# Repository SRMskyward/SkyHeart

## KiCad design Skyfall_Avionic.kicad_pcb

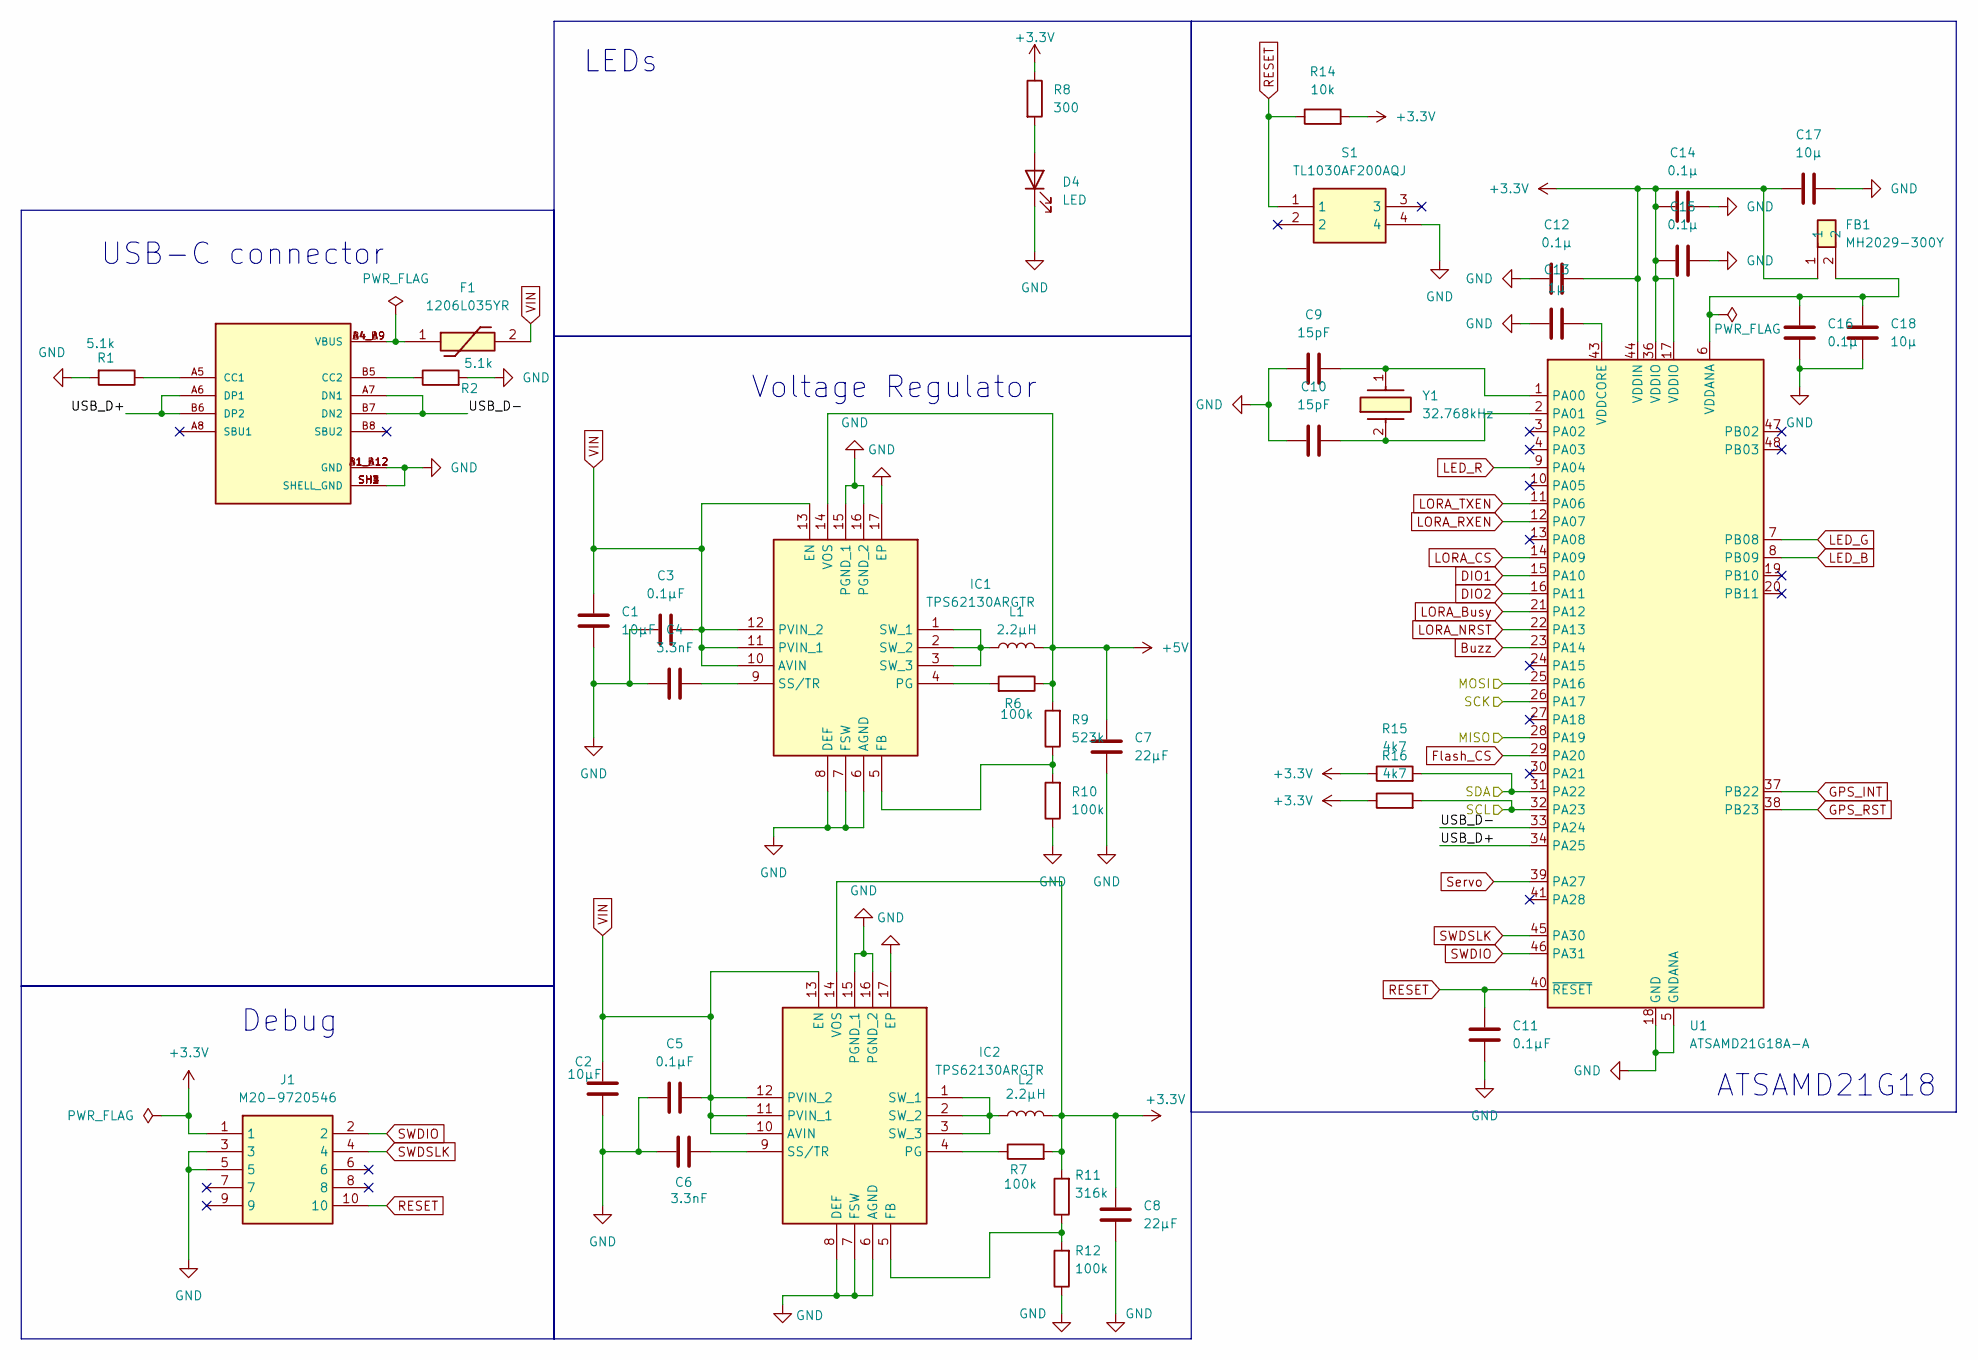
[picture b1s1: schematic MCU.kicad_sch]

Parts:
C1, C2: 10µF; C_0603_1608Metric
C3, C5, C11: 0.1µF; C_0603_1608Metric
C4, C6: 3.3nF; C_0603_1608Metric
C7, C8: 22µF; C_0603_1608Metric
C9, C10: 15pF; C_0603_1608Metric
C12, C14, C15, C16: 0.1µ; C_0603_1608Metric
C13: 1µ; C_0603_1608Metric
C17, C18: 10µ; C_0603_1608Metric
D4: LED; LED_0805_2012Metric
F1: 1206L035YR; 1206L05015YR; Mouser Part Number 576-1206L035YR
FB1: MH2029-300Y; BEADC2016X130N; Mouser Part Number 652-MH2029-300Y
IC1, IC2: TPS62130ARGTR; QFN50P300X300X100-17N-D; Mouser Part Number 595-TPS62130ARGTR
J1: M20-9720546; HDRV10W64P254_2X5_1270X508X954P; Mouser Part Number 855-M20-9720546
J2: USB4105-GF-A-060; GCT_USB4105-GF-A-060; PARTREV B3
L1, L2: 2.2µH; L_TDK_NLV32_3.2x2.5mm
R1, R2: 5.1k; R_0603_1608Metric
R6, R7, R10, R12: 100k; R_0603_1608Metric
R8: 300; R_0603_1608Metric
R9: 523k; R_0603_1608Metric
R11: 316k; R_0603_1608Metric
R14: 10k; R_0603_1608Metric
R15, R16: 4k7; R_0603_1608Metric
S1: TL1030AF200AQJ; Mouser Part Number 612-TL1030AF200AQJ
U1: ATSAMD21G18A-A; TQFP-48_7x7mm_P0.5mm
Y1: 32.768kHz; VMK3900132K7680000; Mouser Part Number 579-K3900132K7680000

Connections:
+3.3V: C8.2, C12.1, C14.2, C15.2, C17.2, FB1.1, IC2.14 (VOS), J1.1, L2.2, R7.2, R8.1, R11.2, R14.2, R15.1, R16.1, U1.17 (VDDIO), U1.36 (VDDIO), U1.44 (VDDIN); also elsewhere on the board
+5V: C7.2, IC1.14 (VOS), L1.2, R6.1, R9.2; also elsewhere on the board
/Actionners_&_connectors/MISO: U1.28 (PA19); also elsewhere on the board
/Actionners_&_connectors/MOSI: U1.25 (PA16); also elsewhere on the board
/Actionners_&_connectors/SCK: U1.26 (PA17); also elsewhere on the board
/Actionners_&_connectors/SCL: R16.2, U1.32 (PA23); also elsewhere on the board
/Actionners_&_connectors/SDA: R15.2, U1.31 (PA22); also elsewhere on the board
/MCU/USB_D+: J2.A6 (DP1), J2.B6 (DP2), U1.34 (PA25)
/MCU/USB_D-: J2.A7 (DN1), J2.B7 (DN2), U1.33 (PA24)
Buzz: U1.23 (PA14); also elsewhere on the board
DIO1: U1.15 (PA10); also elsewhere on the board
DIO2: U1.16 (PA11); also elsewhere on the board
Flash_CS: U1.29 (PA20); also elsewhere on the board
GND: C1.1, C2.1, C3.1, C4.1, C5.1, C6.1, C7.1, C8.1, C9.2, C10.2, C11.2, C12.2, C13.2, C14.1, C15.1, C16.2, C17.1, C18.2, D4.1 (K), IC1.6 (AGND), IC1.7 (FSW), IC1.8 (DEF), IC1.15 (PGND_1), IC1.16 (PGND_2), IC1.17 (EP), IC2.6 (AGND), IC2.7 (FSW), IC2.8 (DEF), IC2.15 (PGND_1), IC2.16 (PGND_2), IC2.17 (EP), J1.3, J1.5, J2.A1_B12 (GND), J2.B1_A12 (GND), J2.SH1 (SHELL_GND), J2.SH2 (SHELL_GND), J2.SH3 (SHELL_GND), J2.SH4 (SHELL_GND), R1.2, R2.2, R10.1, R12.1, S1.4, U1.5 (GNDANA), U1.18 (GND), U1.35 (GND), U1.42 (GND); also elsewhere on the board
GPS_INT: U1.37 (PB22)
GPS_RST: U1.38 (PB23)
LED_B: U1.8 (PB09); also elsewhere on the board
LED_G: U1.7 (PB08); also elsewhere on the board
LED_R: U1.9 (PA04); also elsewhere on the board
LORA_Busy: U1.21 (PA12); also elsewhere on the board
LORA_CS: U1.14 (PA09); also elsewhere on the board
LORA_NRST: U1.22 (PA13); also elsewhere on the board
LORA_RXEN: U1.12 (PA07); also elsewhere on the board
LORA_TXEN: U1.11 (PA06); also elsewhere on the board
unnamed: D4.2 (A), R8.2
unnamed: F1.1, J2.A4_B9 (VBUS), J2.B4_A9 (VBUS)
unnamed: IC1.5 (FB), R9.1, R10.2
unnamed: IC1.4 (PG), R6.2
unnamed: C4.2, IC1.9 (SS/TR)
unnamed: IC1.1 (SW_1), IC1.2 (SW_2), IC1.3 (SW_3), L1.1
unnamed: IC2.5 (FB), R11.1, R12.2
unnamed: IC2.4 (PG), R7.1
unnamed: C6.2, IC2.9 (SS/TR)
unnamed: IC2.1 (SW_1), IC2.2 (SW_2), IC2.3 (SW_3), L2.1
unnamed: J2.A5 (CC1), R1.1
unnamed: J2.B5 (CC2), R2.1
unnamed: C9.1, U1.1 (PA00), Y1.1 (CRYSTAL)
unnamed: C10.1, U1.2 (PA01), Y1.2 (CRYSTAL)
unnamed: C16.1, C18.1, FB1.2, U1.6 (VDDANA)
unnamed: C13.1, U1.43 (VDDCORE)
RESET: C11.1, J1.10, R14.1, S1.1, U1.40 (~RESET)
SWDIO: J1.2, U1.46 (PA31)
SWDSLK: J1.4, U1.45 (PA30)
Servo: U1.39 (PA27); also elsewhere on the board
VIN: C1.2, C2.2, C3.2, C5.2, F1.2, IC1.10 (AVIN), IC1.11 (PVIN_1), IC1.12 (PVIN_2), IC1.13 (EN), IC2.10 (AVIN), IC2.11 (PVIN_1), IC2.12 (PVIN_2), IC2.13 (EN); also elsewhere on the board

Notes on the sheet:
ATSAMD21G18
USB-C connector
LEDs
Voltage Regulator
Debug

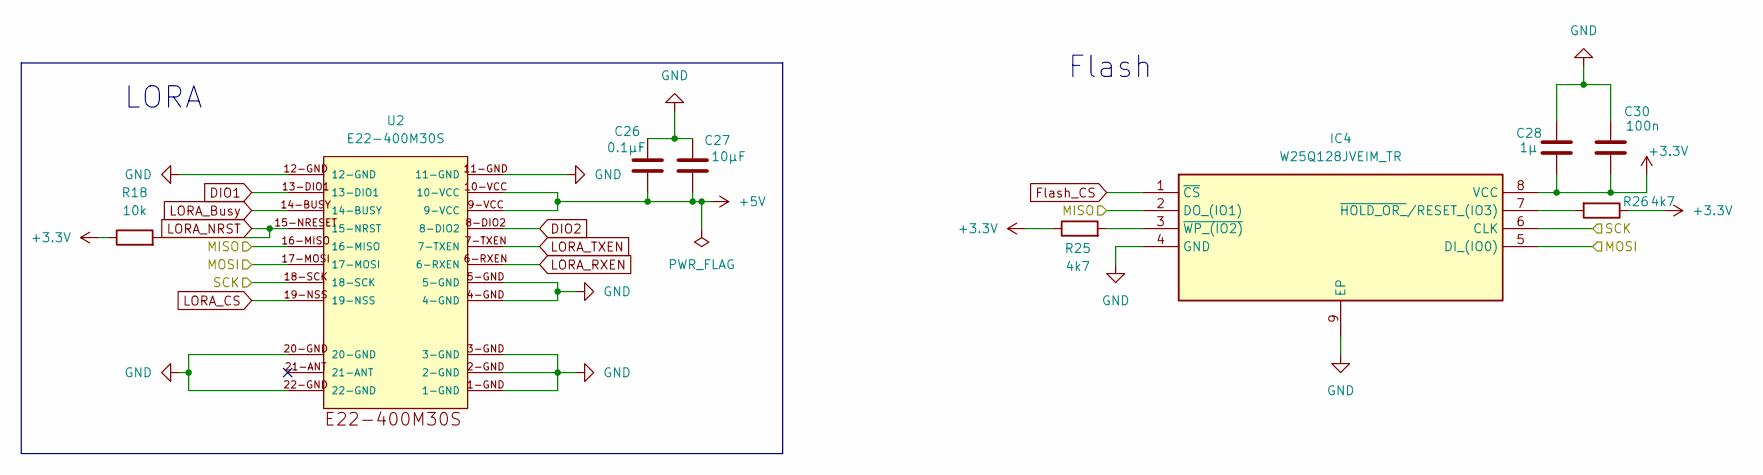
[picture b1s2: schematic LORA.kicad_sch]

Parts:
C26: 0.1µF; C_0603_1608Metric
C27: 10µF; C_0603_1608Metric
C28: 1µ; C_0603_1608Metric
C30: 100n; C_0603_1608Metric
IC4: W25Q128JVEIM_TR; SON127P800X600X80-9N-D; Mouser Part Number 454-W25Q128JVEIMTR
R18: 10k; R_0603_1608Metric
R25, R26: 4k7; R_0603_1608Metric
U2: E22-400M30S

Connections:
+3.3V: C28.1, C30.1, IC4.8 (VCC), R18.1, R25.1, R26.1; also elsewhere on the board
+5V: C26.1, C27.1, U2.9-VCC, U2.10-VCC; also elsewhere on the board
/Actionners_&_connectors/MISO: IC4.2 (DO_(IO1)), U2.16-MISO; also elsewhere on the board
/Actionners_&_connectors/MOSI: IC4.5 (DI_(IO0)), U2.17-MOSI; also elsewhere on the board
/Actionners_&_connectors/SCK: IC4.6 (CLK), U2.18-SCK; also elsewhere on the board
DIO1: U2.13-DIO1; also elsewhere on the board
DIO2: U2.8-DIO2; also elsewhere on the board
Flash_CS: IC4.1 (~CS); also elsewhere on the board
GND: C26.2, C27.2, C28.2, C30.2, IC4.4 (GND), IC4.9 (EP), U2.1-GND, U2.2-GND, U2.3-GND, U2.4-GND, U2.5-GND, U2.11-GND, U2.12-GND, U2.20-GND, U2.22-GND; also elsewhere on the board
LORA_Busy: U2.14-BUSY; also elsewhere on the board
LORA_CS: U2.19-NSS; also elsewhere on the board
LORA_NRST: R18.2, U2.15-NRESET (15-NRST); also elsewhere on the board
LORA_RXEN: U2.6-RXEN; also elsewhere on the board
LORA_TXEN: U2.7-TXEN; also elsewhere on the board
unnamed: IC4.7 (~HOLD_OR_/RESET_(IO3)), R26.2
unnamed: IC4.3 (~WP_(IO2)), R25.2

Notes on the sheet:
LORA
Flash

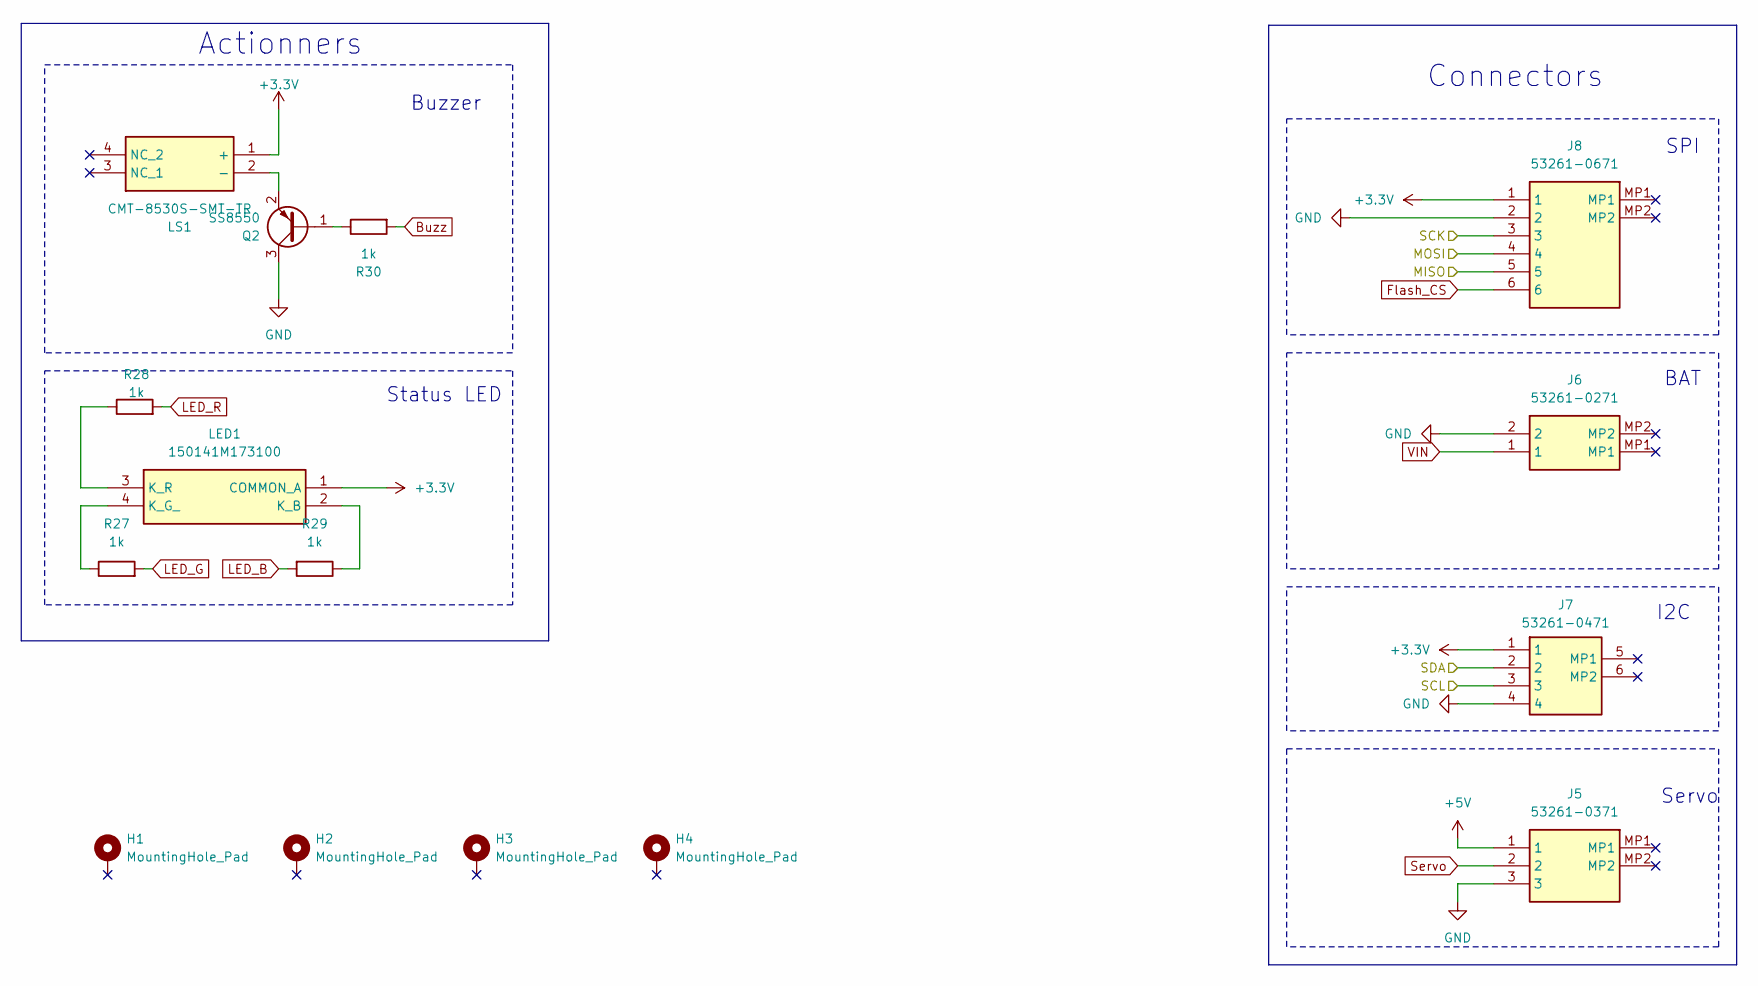
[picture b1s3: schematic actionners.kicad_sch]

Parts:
H1, H2, H3, H4: MountingHole_Pad; MountingHole_2.7mm_M2.5_Pad
J5: 53261-0371; 532610371; Mouser Part Number 538-53261-0371
J6: 53261-0271; 532610271; Mouser Part Number 538-53261-0271
J7: 53261-0471; Mouser Part Number 538-53261-0471
J8: 53261-0671; 532610671; Mouser Part Number 538-53261-0671
LED1: 150141M173100; Mouser Part Number 710-150141M173100
LS1: CMT-8530S-SMT-TR; CMT8530SSMTTR; Mouser Part Number 490-CMT-8530S-SMT-TR
Q2: SS8550; SOT-23
R27, R28, R29, R30: 1k; R_0603_1608Metric

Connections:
+3.3V: J7.1, J8.1, LED1.1 (COMMON_A), LS1.1 (+); also elsewhere on the board
+5V: J5.1; also elsewhere on the board
/Actionners_&_connectors/MISO: J8.5; also elsewhere on the board
/Actionners_&_connectors/MOSI: J8.4; also elsewhere on the board
/Actionners_&_connectors/SCK: J8.3; also elsewhere on the board
/Actionners_&_connectors/SCL: J7.3; also elsewhere on the board
/Actionners_&_connectors/SDA: J7.2; also elsewhere on the board
Buzz: R30.2; also elsewhere on the board
Flash_CS: J8.6; also elsewhere on the board
GND: H1.1, H2.1, H3.1, H4.1, J5.3, J6.2, J7.4, J8.2, Q2.3 (C); also elsewhere on the board
LED_B: R29.2; also elsewhere on the board
LED_G: R27.2; also elsewhere on the board
LED_R: R28.2; also elsewhere on the board
unnamed: LED1.2 (K_B), R29.1
unnamed: LED1.4 (K_G_), R27.1
unnamed: LED1.3 (K_R), R28.1
unnamed: LS1.2 (-), Q2.2 (E)
unnamed: Q2.1 (B), R30.1
Servo: J5.2; also elsewhere on the board
VIN: J6.1; also elsewhere on the board

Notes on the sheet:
Buzzer
Actionners
Status LED
BAT
SPI
Servo
I2C
Connectors

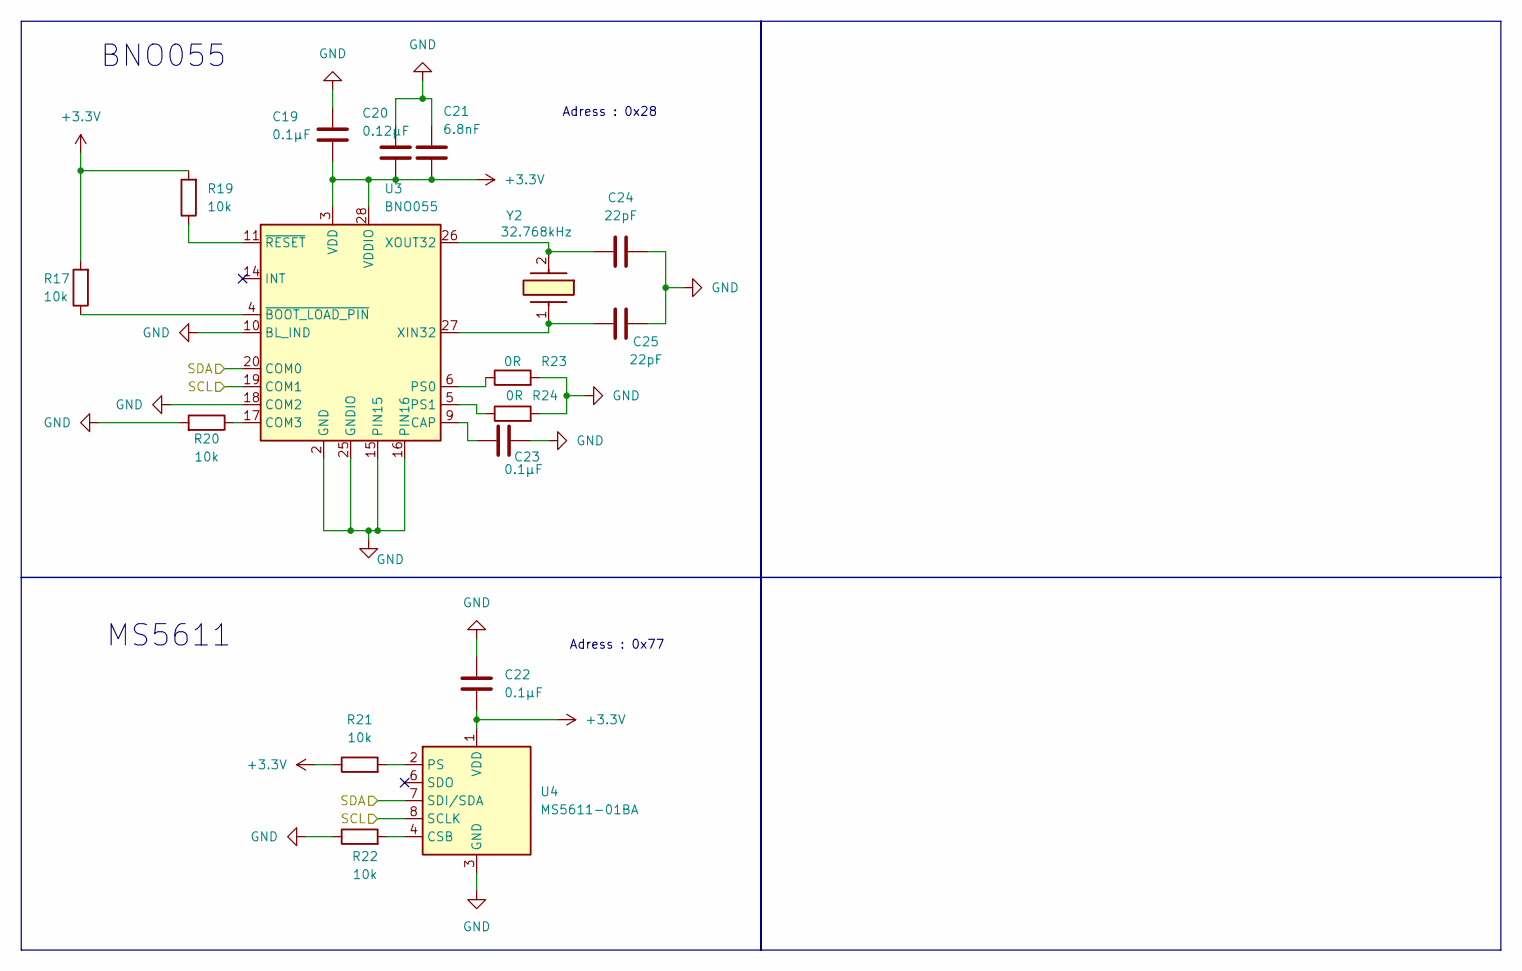
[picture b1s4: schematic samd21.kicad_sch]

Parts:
C19, C22, C23: 0.1µF; C_0603_1608Metric
C20: 0.12µF; C_0603_1608Metric
C21: 6.8nF; C_0603_1608Metric
C24, C25: 22pF; C_0603_1608Metric
R17, R19, R20, R21, R22: 10k; R_0603_1608Metric
R23, R24: 0R; R_0603_1608Metric
U3: BNO055; LGA-28_5.2x3.8mm_P0.5mm
U4: MS5611-01BA; LGA-8_3x5mm_P1.25mm
Y2: 32.768kHz; VMK3900132K7680000; Mouser Part Number 579-K3900132K7680000

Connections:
+3.3V: C19.1, C20.1, C21.1, C22.1, R17.2, R19.2, R21.1, U3.3 (VDD), U3.28 (VDDIO), U4.1 (VDD); also elsewhere on the board
/Actionners_&_connectors/SCL: U3.19 (COM1), U4.8 (SCLK); also elsewhere on the board
/Actionners_&_connectors/SDA: U3.20 (COM0), U4.7 (SDI/SDA); also elsewhere on the board
GND: C19.2, C20.2, C21.2, C22.2, C23.2, C24.2, C25.2, R20.2, R22.1, R23.2, R24.2, U3.2 (GND), U3.10 (BL_IND), U3.15 (PIN15), U3.16 (PIN16), U3.18 (COM2), U3.25 (GNDIO), U4.3 (GND); also elsewhere on the board
unnamed: R22.2, U4.4 (CSB), U4.5 (CSB)
unnamed: C23.1, U3.9 (CAP)
unnamed: R20.1, U3.17 (COM3)
unnamed: R23.1, U3.6 (PS0)
unnamed: R24.1, U3.5 (PS1)
unnamed: C25.1, U3.27 (XIN32), Y2.1 (CRYSTAL)
unnamed: C24.1, U3.26 (XOUT32), Y2.2 (CRYSTAL)
unnamed: R17.1, U3.4 (~BOOT_LOAD_PIN)
unnamed: R19.1, U3.11 (~RESET)
unnamed: R21.2, U4.2 (PS)

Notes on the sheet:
BNO055
Adress : 0x77
MS5611
Adress : 0x28

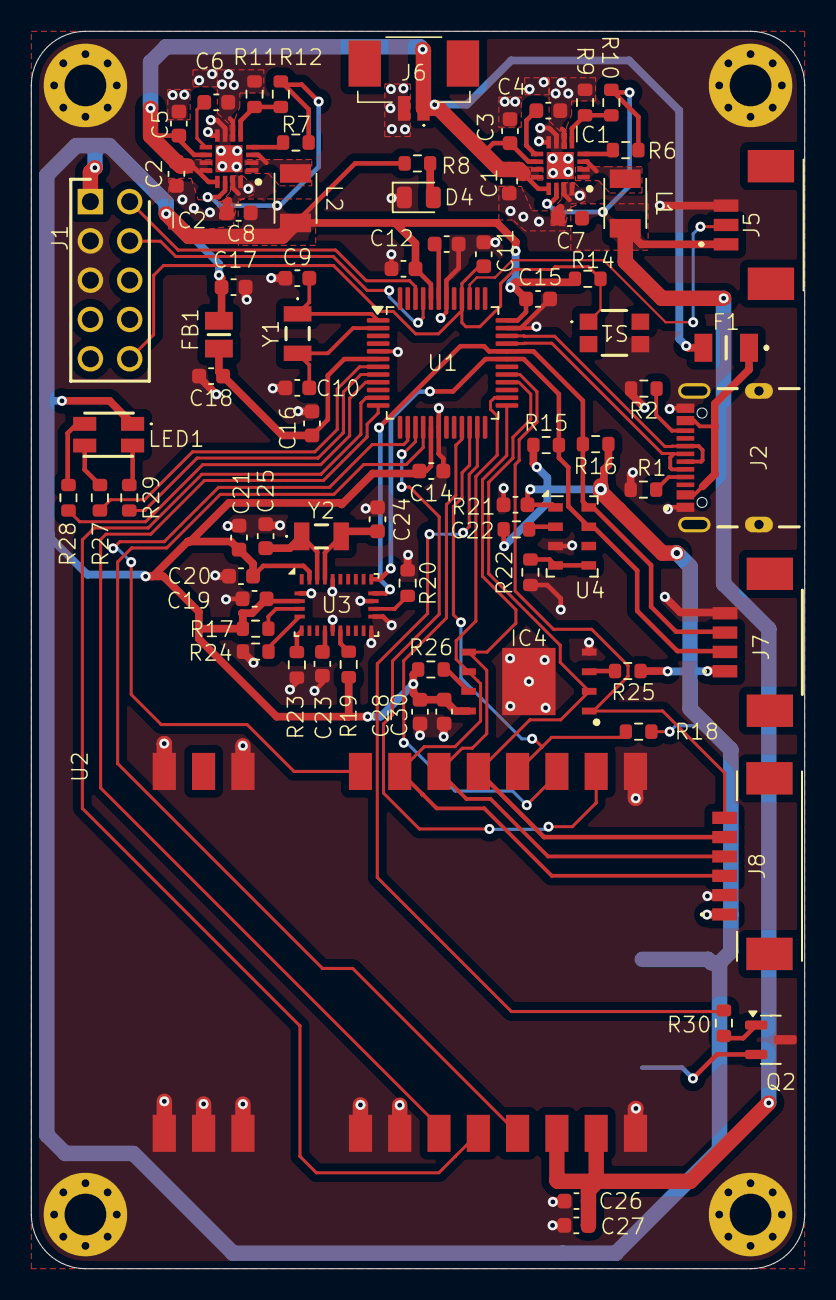
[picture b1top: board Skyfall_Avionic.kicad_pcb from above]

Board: 2 copper layers, 50.0 x 80.0 mm, 83 parts (1 on the bottom side), 60 nets.

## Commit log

2025-07-16 First draft
2025-07-16 Minor PCB Changes
2025-07-16 PCB Review
2025-07-17 Review
